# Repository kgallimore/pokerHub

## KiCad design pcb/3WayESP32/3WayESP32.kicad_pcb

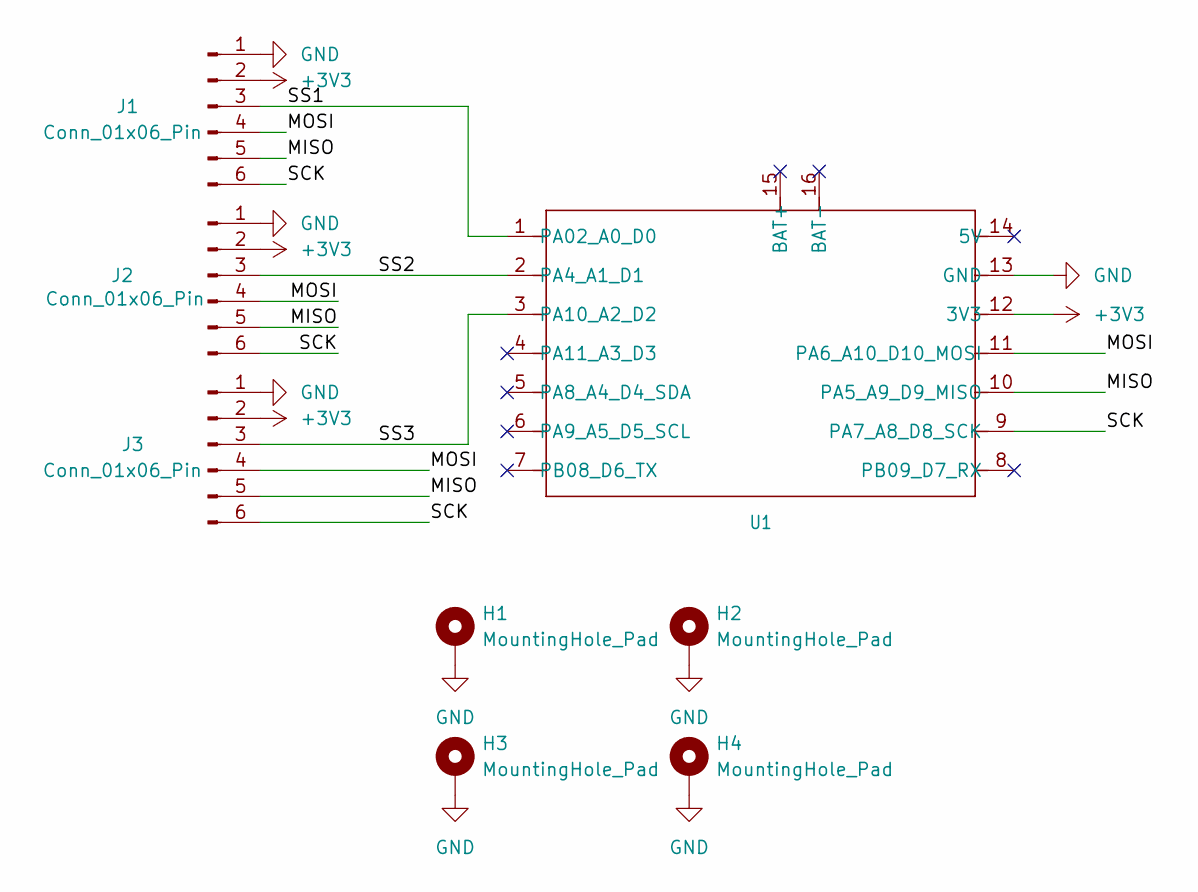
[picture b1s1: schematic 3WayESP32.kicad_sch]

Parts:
H1, H2: MountingHole_Pad; MountingHole_3.2mm_M3_DIN965_Pad
H3, H4: MountingHole_Pad; MountingHole_3.2mm_M3_Pad
J1, J2, J3: Conn_01x06_Pin; PinHeader_1x06_P2.54mm_Horizontal
U1: MOUDLE14P-SMD-2.54-21X17.8MM

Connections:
+3V3: J1.2, J2.2, J3.2, U1.12 (3V3)
/MISO: J1.5, J2.5, J3.5, U1.10 (PA5_A9_D9_MISO)
/MOSI: J1.4, J2.4, J3.4, U1.11 (PA6_A10_D10_MOSI)
/SCK: J1.6, J2.6, J3.6, U1.9 (PA7_A8_D8_SCK)
/SS1: J1.3, U1.1 (PA02_A0_D0)
/SS2: J2.3, U1.2 (PA4_A1_D1)
/SS3: J3.3, U1.3 (PA10_A2_D2)
GND: H1.1, H2.1, H3.1, H4.1, J1.1, J2.1, J3.1, U1.13 (GND)

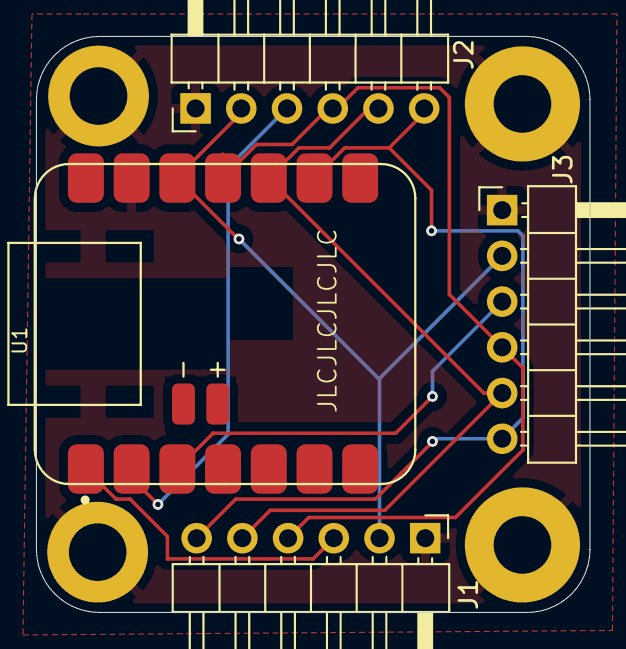
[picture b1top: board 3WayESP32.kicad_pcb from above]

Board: 2 copper layers, 30.8 x 32.0 mm, 8 parts (0 on the bottom side), 8 nets.

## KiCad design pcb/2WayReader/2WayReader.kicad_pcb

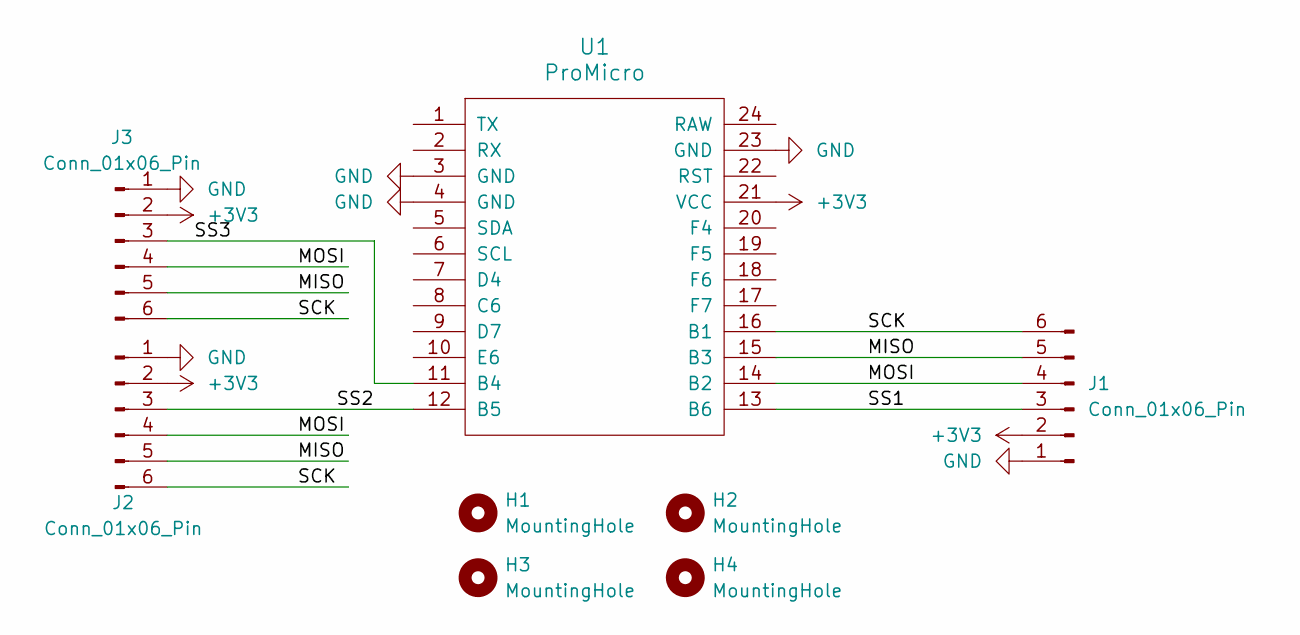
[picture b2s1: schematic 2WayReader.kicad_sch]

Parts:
H1, H2, H3, H4: MountingHole; MountingHole_3.2mm_M3
J1, J2, J3: Conn_01x06_Pin; PinHeader_1x06_P2.54mm_Horizontal
U1: ProMicro

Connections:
+3V3: J1.2, J2.2, J3.2, U1.21 (VCC)
/MISO: J1.5, J2.5, J3.5, U1.15 (B3)
/MOSI: J1.4, J2.4, J3.4, U1.14 (B2)
/SCK: J1.6, J2.6, J3.6, U1.16 (B1)
/SS1: J1.3, U1.13 (B6)
/SS2: J2.3, U1.12 (B5)
/SS3: J3.3, U1.11 (B4)
GND: J1.1, J2.1, J3.1, U1.3 (GND), U1.4 (GND), U1.23 (GND)

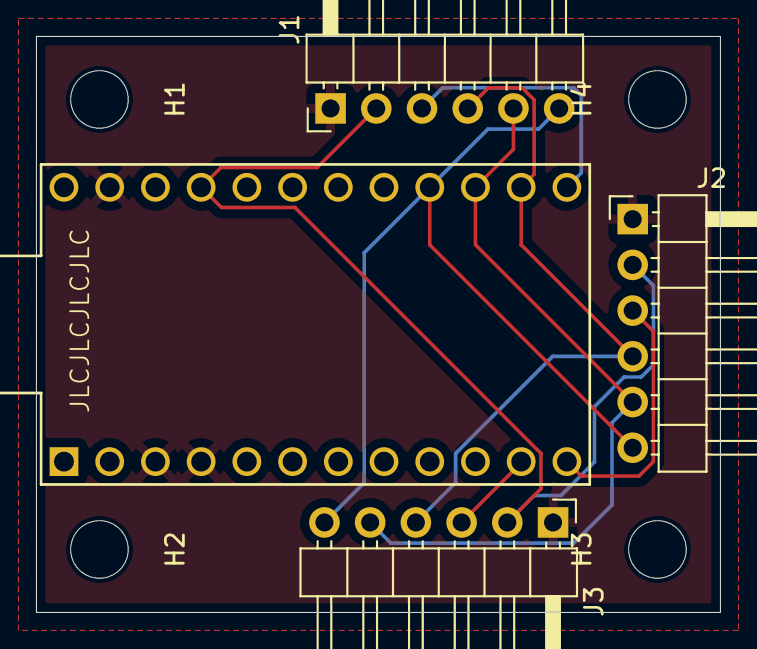
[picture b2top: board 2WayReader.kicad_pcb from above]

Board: 2 copper layers, 38.0 x 32.0 mm, 8 parts (0 on the bottom side), 8 nets.

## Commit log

2023-05-31 Init
2023-06-02 Typescript
2023-06-02 Test
2023-06-02 Remove Test
2023-06-02 init svelte
2023-06-18 Move directories
2023-06-18 Generate Cards
2023-06-18 Add Arduino and card info
2023-06-21 Init prisma
2023-06-23 CommPort Api init
2023-06-25 Display cards
2023-06-26 2 cards per reader
2023-10-25 Octagon poker table
2024-07-06 Update to platformio
2024-07-07 Revamp svelte
2024-07-07 Switch to pocketbase
2024-07-08 Update comm
2024-07-09 threlte
2024-07-13 Working 3d
2024-07-13 2d table updates
2024-07-16 esp reader
2024-07-16 Task testing
2024-07-16 New lib
2024-07-16 Plated mounting holes
2024-07-18 Sensor hub updates
2024-07-18 Reorg
2024-07-19 Update prod run files
2024-07-19 Update packages
2024-07-19 Update scripts
2024-07-19 Make scripts executable by default
2024-07-19 Fix prod bun command
2024-07-19 Comm read esp32
2024-07-19 Bun can't run comm
2024-07-19 pm2 changes
2024-07-30 Remove ESP32
